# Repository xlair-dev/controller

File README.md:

# controller

Hardware and firmware for each controller revision.

```text
.
├── kicad-lib/       # Shared KiCad libraries
├── v1/
│   ├── pcb/         # v1 KiCad project
│   └── firmware/    # v1 firmware
└── v2/
    ├── pcb/         # v2 KiCad project
    └── firmware/    # v2 firmware
```

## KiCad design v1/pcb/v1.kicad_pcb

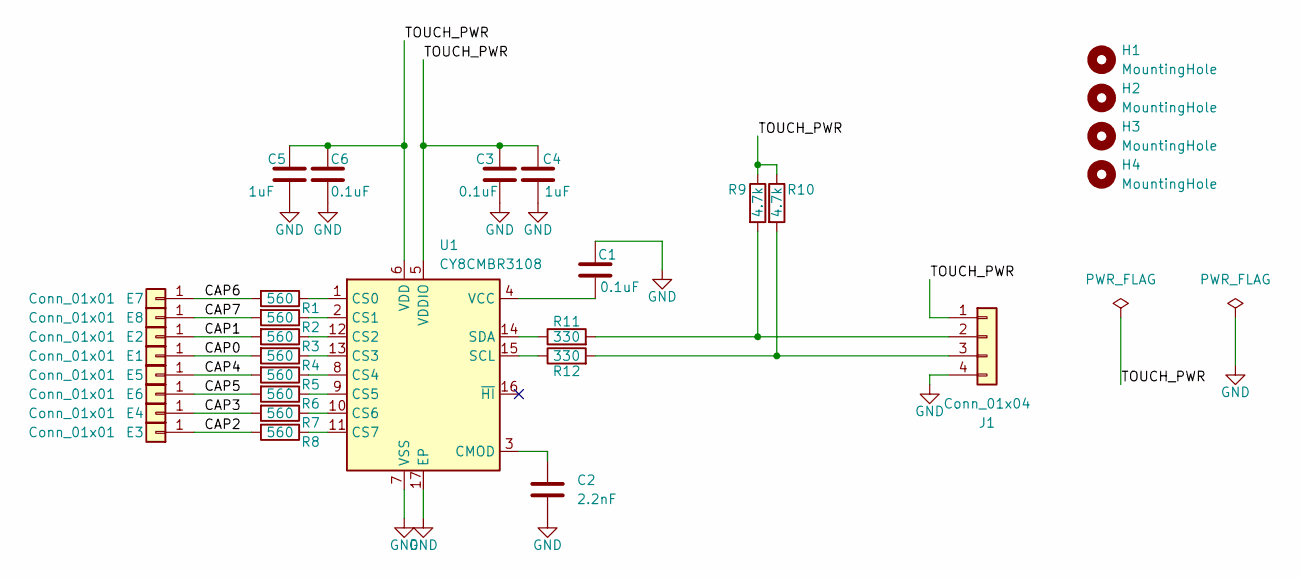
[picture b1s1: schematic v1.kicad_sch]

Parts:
C1, C3, C5: 0.1uF; C_0603_1608Metric
C2: 2.2nF; C_0603_1608Metric
C4, C6: 1uF; C_0603_1608Metric
E1, E2, E3, E4, E5, E6, E7, E8: Conn_01x01; TouchPad
H1, H2, H3, H4: MountingHole; MountingHole_3.2mm_M3
J1: Conn_01x04; JST_XH_B4B-XH-A_1x04_P2.50mm_Vertical
R1, R2, R3, R4, R5, R6, R7, R8: 560; R_0603_1608Metric
R9, R10: 4.7k; R_Axial_DIN0207_L6.3mm_D2.5mm_P10.16mm_Horizontal
R11, R12: 330; R_0603_1608Metric
U1: CY8CMBR3108; QFN-16-1EP_3x3mm_P0.5mm_EP1.7x1.7mm

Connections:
/CAP0: E1.1 (Pin_1_1), R4.2
/CAP1: E2.1 (Pin_1_1), R3.2
/CAP2: E3.1 (Pin_1_1), R8.2
/CAP3: E4.1 (Pin_1_1), R7.2
/CAP4: E5.1 (Pin_1_1), R5.2
/CAP5: E6.1 (Pin_1_1), R6.2
/CAP6: E7.1 (Pin_1_1), R1.2
/CAP7: E8.1 (Pin_1_1), R2.2
/TOUCH_PWR: C3.1, C4.1, C5.1, C6.1, J1.1, R9.1, R10.1, U1.5 (VDDIO), U1.6 (VDD)
GND: C1.1, C2.2, C3.2, C4.2, C5.2, C6.2, J1.4, U1.7 (VSS), U1.17 (EP)
unnamed: J1.2, R9.2, R11.2
unnamed: J1.3, R10.2, R12.2
unnamed: C2.1, U1.3 (CMOD)
unnamed: R1.1, U1.1 (CS0)
unnamed: R2.1, U1.2 (CS1)
unnamed: R3.1, U1.12 (CS2)
unnamed: R4.1, U1.13 (CS3)
unnamed: R5.1, U1.8 (CS4)
unnamed: R6.1, U1.9 (CS5)
unnamed: R7.1, U1.10 (CS6)
unnamed: R8.1, U1.11 (CS7)
unnamed: R12.1, U1.15 (SCL)
unnamed: R11.1, U1.14 (SDA)
unnamed: C1.2, U1.4 (VCC)

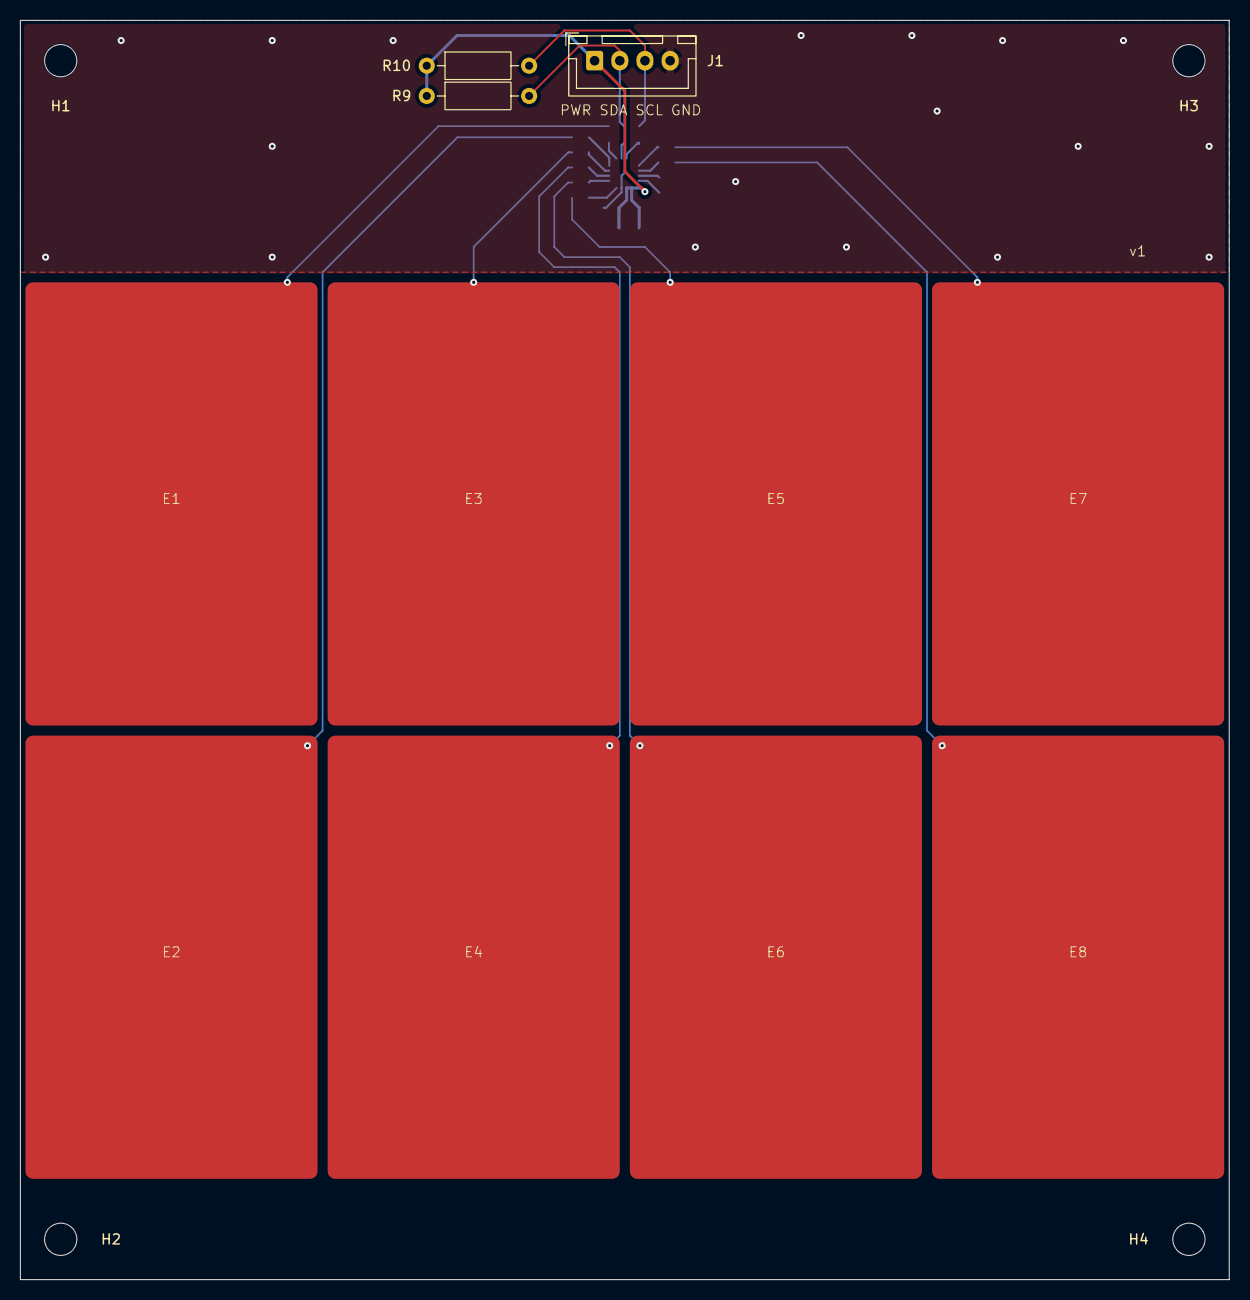
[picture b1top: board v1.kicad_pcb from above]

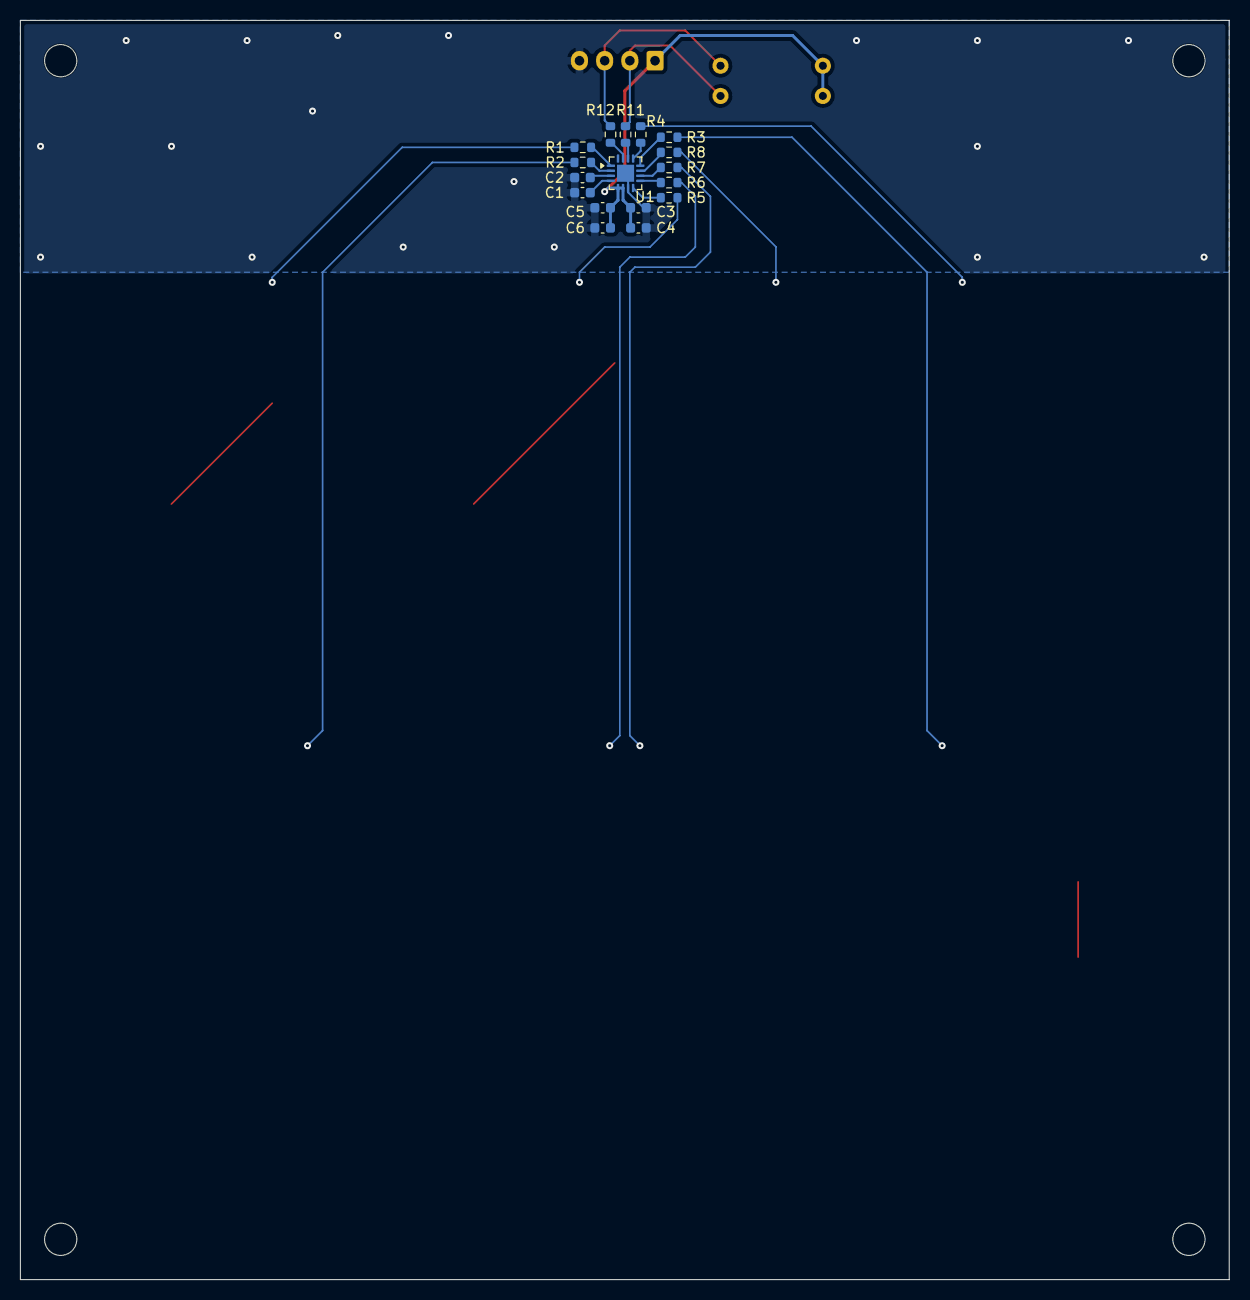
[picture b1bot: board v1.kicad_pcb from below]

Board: 2 copper layers, 120.0 x 125.0 mm, 32 parts (17 on the bottom side), 24 nets.
